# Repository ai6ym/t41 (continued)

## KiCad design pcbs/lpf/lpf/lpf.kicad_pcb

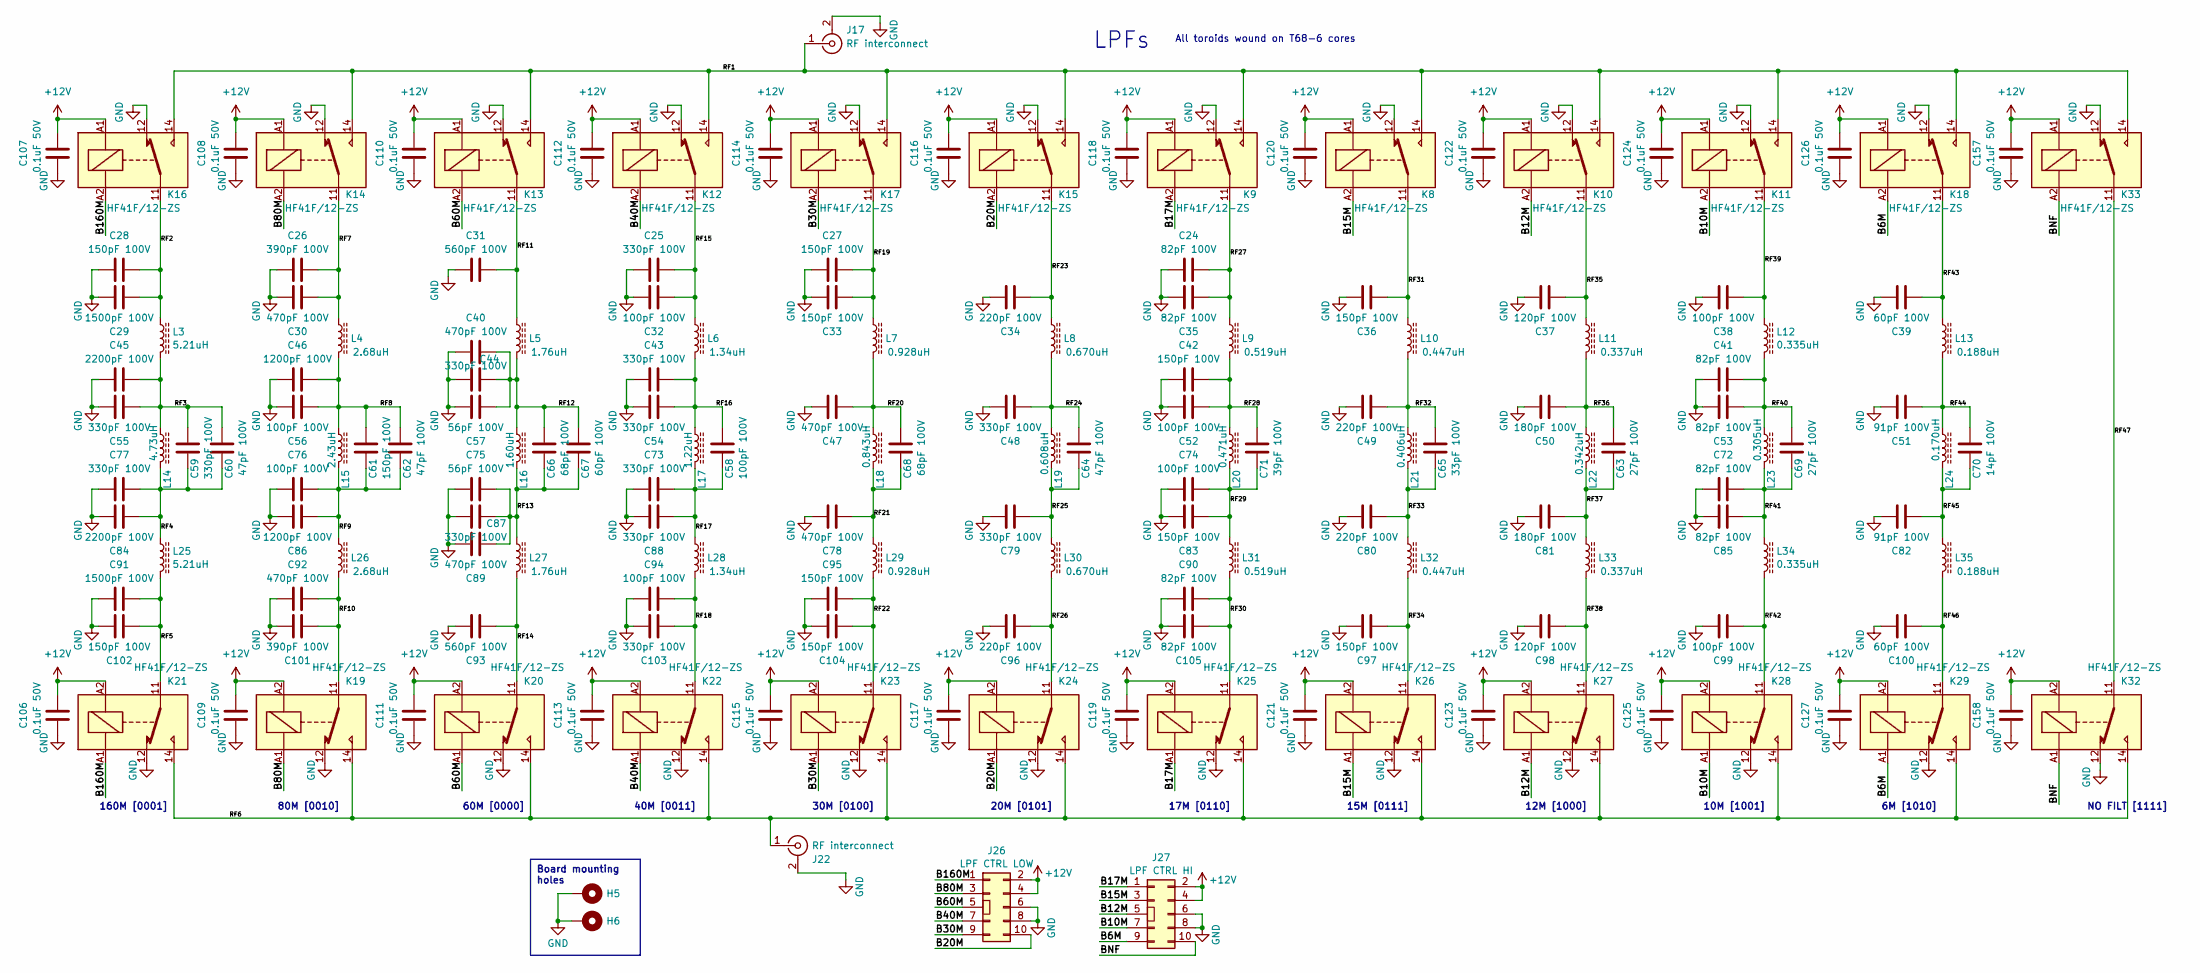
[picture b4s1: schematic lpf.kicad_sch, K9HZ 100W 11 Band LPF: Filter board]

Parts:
C24, C35, C41, C53, C72, C85, C90, C105: 82pF 100V; C_1206_3216Metric; Mouser Part Number 80-C1206C820J1G
C25, C43, C44, C48, C54, C55, C59, C73, C77, C79, C87, C88, C103: 330pF 100V; C_1206_3216Metric; Mouser Part Number 581-12061A331JAT4A
C26, C101: 390pF 100V; C_1206_3216Metric; Mouser Part Number 80-C1206C391J1G
C27, C28, C33, C36, C42, C61, C83, C95, C97, C102, C104: 150pF 100V; C_1206_3216Metric; Mouser Part Number 80-C1206C151J1G
C29, C91: 1500pF 100V; C_1206_3216Metric; Mouser Part Number 80-C1206C152J1GECAUT
C30, C40, C47, C78, C89, C92: 470pF 100V; C_1206_3216Metric; Mouser Part Number 80-C1206C471J1GAC
C31, C93: 560pF 100V; C_1206_3216Metric; Mouser Part Number 581-12061C561JAT2A
C32, C38, C52, C56, C58, C74, C76, C94, C99: 100pF 100V; C_1206_3216Metric; Mouser Part Number 80-C1206C101J1GAULR
C34, C49, C80, C96: 220pF 100V; C_1206_3216Metric; Mouser Part Number 80-C1206C221J1GAC
C37, C98: 120pF 100V; C_1206_3216Metric; Mouser Part Number 77-VJ1206A121JXBMT
C39, C67, C100: 60pF 100V; C_1206_3216Metric; Mouser Part Number 80-C1206C620J1G
C45, C84: 2200pF 100V; C_1206_3216Metric; Mouser Part Number 81-GRM319R72A222JA1D
C46, C86: 1200pF 100V; C_1206_3216Metric; Mouser Part Number 581-12061C122JAT2A
C50, C81: 180pF 100V; C_1206_3216Metric; Mouser Part Number 80-C1206C181J1G
C51, C82: 91pF 100V; C_1206_3216Metric; Mouser Part Number 80-C1206C910J1G
C57, C75: 56pF 100V; C_1206_3216Metric; Mouser Part Number 80-C1206C560J1G
C60, C62, C64: 47pF 100V; C_1206_3216Metric; Mouser Part Number 80-C1206C470J1GAC
C63, C69: 27pF 100V; C_1206_3216Metric; Mouser Part Number 80-C1206C270J1G
C65: 33pF 100V; C_1206_3216Metric; Mouser Part Number 80-C1206C330J1G
C66, C68: 68pF 100V; C_1206_3216Metric; Mouser Part Number 80-C1206C680J1G
C70: 14pF 100V; C_0805_2012Metric; Mouser Part Number 80-C1206C150J1G
C71: 39pF 100V; C_1206_3216Metric; Mouser Part Number 80-C1206C390J1G
C106, C107, C108, C109, C110, C111, C112, C113, C114, C115, C116, C117, C118, C119, C120, C121, C122, C123, C124, C125, C126, C127, C157, C158: 0.1uF 50V; C_1206_3216Metric; Mouser Part Number 581-12065F104K4
H5, H6: MountingHole_4.3mm_M4_DIN965_Pad
J17, J22: RF interconnect; SMA_Amphenol_901-144_Vertical; Mouser Part Number 712-CONSMA001-G
J26: LPF CTRL LOW; IDC-Header_2x05_P2.54mm_Vertical
J27: LPF CTRL HI; IDC-Header_2x05_P2.54mm_Vertical
K8, K9, K10, K11, K12, K13, K14, K15, K16, K17, K18, K19, K20, K21, K22, K23, K24, K25, K26, K27, K28, K29, K32, K33: HF41F/12-ZS; Relay_SPDT_HF41F12-ZS
L3, L25: 5.21uH; T68-6-toroid-vertical
L4, L26: 2.68uH; T68-6-toroid-vertical
L5, L27: 1.76uH; T68-6-toroid-vertical
L6, L28: 1.34uH; T68-6-toroid-vertical
L7, L29: 0.928uH; T68-6-toroid-vertical
L8, L30: 0.670uH; T68-6-toroid-vertical
L9, L31: 0.519uH; T68-6-toroid-vertical
L10, L32: 0.447uH; T68-6-toroid-vertical
L11, L33: 0.337uH; T68-6-toroid-vertical
L12, L34: 0.335uH; T68-6-toroid-vertical
L13, L35: 0.188uH; T68-6-toroid-vertical
L14: 4.73uH; T68-6-toroid-vertical
L15: 2.43uH; T68-6-toroid-vertical
L16: 1.60uH; T68-6-toroid-vertical
L17: 1.22uH; T68-6-toroid-vertical
L18: 0.843uH; T68-6-toroid-vertical
L19: 0.608uH; T68-6-toroid-vertical
L20: 0.471uH; T68-6-toroid-vertical
L21: 0.406uH; T68-6-toroid-vertical
L22: 0.342uH; T68-6-toroid-vertical
L23: 0.305uH; T68-6-toroid-vertical
L24: 0.170uH; T68-6-toroid-vertical

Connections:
+12V: C106.1, C107.1, C108.1, C109.1, C110.1, C111.1, C112.1, C113.1, C114.1, C115.1, C116.1, C117.1, C118.1, C119.1, C120.1, C121.1, C122.1, C123.1, C124.1, C125.1, C126.1, C127.1, C157.1, C158.1, J26.2, J26.4, J27.2, J27.4, K8.A1, K9.A1, K10.A1, K11.A1, K12.A1, K13.A1, K14.A1, K15.A1, K16.A1, K17.A1, K18.A1, K19.A2, K20.A2, K21.A2, K22.A2, K23.A2, K24.A2, K25.A2, K26.A2, K27.A2, K28.A2, K29.A2, K32.A2, K33.A1
/B6M: J27.9, K18.A2, K29.A1
/B10M: J27.7, K11.A2, K28.A1
/B12M: J27.5, K10.A2, K27.A1
/B15M: J27.3, K8.A2, K26.A1
/B17M: J27.1, K9.A2, K25.A1
/B20M: J26.10, K15.A2, K24.A1
/B30M: J26.9, K17.A2, K23.A1
/B40M: J26.7, K12.A2, K22.A1
/B60M: J26.5, K13.A2, K20.A1
/B80M: J26.3, K14.A2, K19.A1
/B160M: J26.1, K16.A2, K21.A1
/BNF: J27.10, K32.A1, K33.A2
/RF1: J17.1 (In), K8.14, K9.14, K10.14, K11.14, K12.14, K13.14, K14.14, K15.14, K16.14, K17.14, K18.14, K33.14
/RF2: C28.2, C29.2, K16.11, L3.1
/RF3: C45.2, C55.2, C59.2, C60.2, L3.2, L14.1
/RF4: C59.1, C60.1, C77.2, C84.2, L14.2, L25.1
/RF5: C91.2, C102.2, K21.11, L25.2
/RF6: J22.1 (In), K19.14, K20.14, K21.14, K22.14, K23.14, K24.14, K25.14, K26.14, K27.14, K28.14, K29.14, K32.14
/RF7: C26.2, C30.2, K14.11, L4.1
/RF8: C46.2, C56.2, C61.2, C62.2, L4.2, L15.1
/RF9: C61.1, C62.1, C76.2, C86.2, L15.2, L26.1
/RF10: C92.2, C101.2, K19.11, L26.2
/RF11: C31.2, K13.11, L5.1
/RF12: C40.2, C44.2, C57.2, C66.2, C67.2, L5.2, L16.1
/RF13: C66.1, C67.1, C75.2, C87.2, C89.2, L16.2, L27.1
/RF14: C93.2, K20.11, L27.2
/RF15: C25.2, C32.2, K12.11, L6.1
/RF16: C43.2, C54.2, C58.2, L6.2, L17.1
/RF17: C58.1, C73.2, C88.2, L17.2, L28.1
/RF18: C94.2, C103.2, K22.11, L28.2
/RF19: C27.2, C33.2, K17.11, L7.1
/RF20: C47.2, C68.2, L7.2, L18.1
/RF21: C68.1, C78.2, L18.2, L29.1
/RF22: C95.2, C104.2, K23.11, L29.2
/RF23: C34.2, K15.11, L8.1
/RF24: C48.2, C64.2, L8.2, L19.1
/RF25: C64.1, C79.2, L19.2, L30.1
/RF26: C96.2, K24.11, L30.2
/RF27: C24.2, C35.2, K9.11, L9.1
/RF28: C42.2, C52.2, C71.2, L9.2, L20.1
/RF29: C71.1, C74.2, C83.2, L20.2, L31.1
/RF30: C90.2, C105.2, K25.11, L31.2
/RF31: C36.2, K8.11, L10.1
/RF32: C49.2, C65.2, L10.2, L21.1
/RF33: C65.1, C80.2, L21.2, L32.1
/RF34: C97.2, K26.11, L32.2
/RF35: C37.2, K10.11, L11.1
/RF36: C50.2, C63.2, L11.2, L22.1
/RF37: C63.1, C81.2, L22.2, L33.1
/RF38: C98.2, K27.11, L33.2
/RF39: C38.2, K11.11, L12.1
/RF40: C41.2, C53.2, C69.2, L12.2, L23.1
/RF41: C69.1, C72.2, C85.2, L23.2, L34.1
/RF42: C99.2, K28.11, L34.2
/RF43: C39.2, K18.11, L13.1
/RF44: C51.2, C70.2, L13.2, L24.1
/RF45: C70.1, C82.2, L24.2, L35.1
/RF46: C100.2, K29.11, L35.2
/RF47: K32.11, K33.11
GND: C24.1, C25.1, C26.1, C27.1, C28.1, C29.1, C30.1, C31.1, C32.1, C33.1, C34.1, C35.1, C36.1, C37.1, C38.1, C39.1, C40.1, C41.1, C42.1, C43.1, C44.1, C45.1, C46.1, C47.1, C48.1, C49.1, C50.1, C51.1, C52.1, C53.1, C54.1, C55.1, C56.1, C57.1, C72.1, C73.1, C74.1, C75.1, C76.1, C77.1, C78.1, C79.1, C80.1, C81.1, C82.1, C83.1, C84.1, C85.1, C86.1, C87.1, C88.1, C89.1, C90.1, C91.1, C92.1, C93.1, C94.1, C95.1, C96.1, C97.1, C98.1, C99.1, C100.1, C101.1, C102.1, C103.1, C104.1, C105.1, C106.2, C107.2, C108.2, C109.2, C110.2, C111.2, C112.2, C113.2, C114.2, C115.2, C116.2, C117.2, C118.2, C119.2, C120.2, C121.2, C122.2, C123.2, C124.2, C125.2, C126.2, C127.2, C157.2, C158.2, H5.1, H6.1, J17.2 (Ext), J22.2 (Ext), J26.6, J26.8, J27.6, J27.8, K8.12, K9.12, K10.12, K11.12, K12.12, K13.12, K14.12, K15.12, K16.12, K17.12, K18.12, K19.12, K20.12, K21.12, K22.12, K23.12, K24.12, K25.12, K26.12, K27.12, K28.12, K29.12, K32.12, K33.12

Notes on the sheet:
Board mounting holes
6M [1010]
160M [0001]
15M [0111]
All toroids wound on T68-6 cores
10M [1001]
30M [0100]
20M [0101]
40M [0011]
60M [0000]
LPFs
17M [0110]
12M [1000]
80M [0010]
NO FILT [1111]

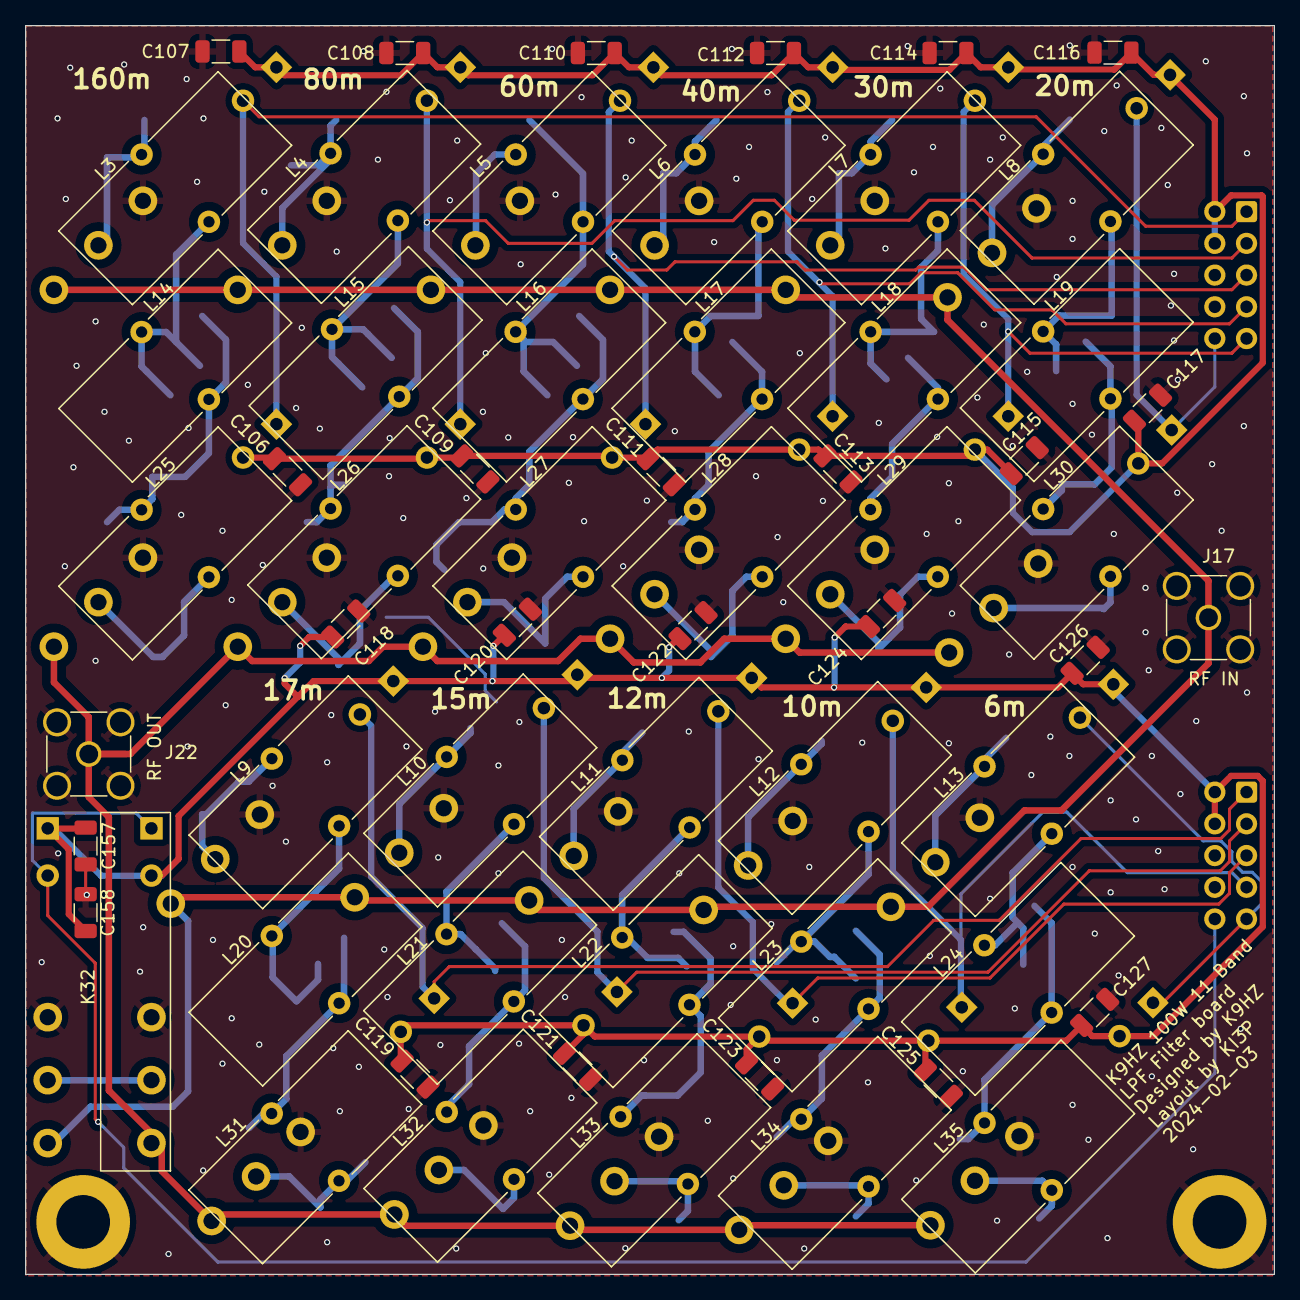
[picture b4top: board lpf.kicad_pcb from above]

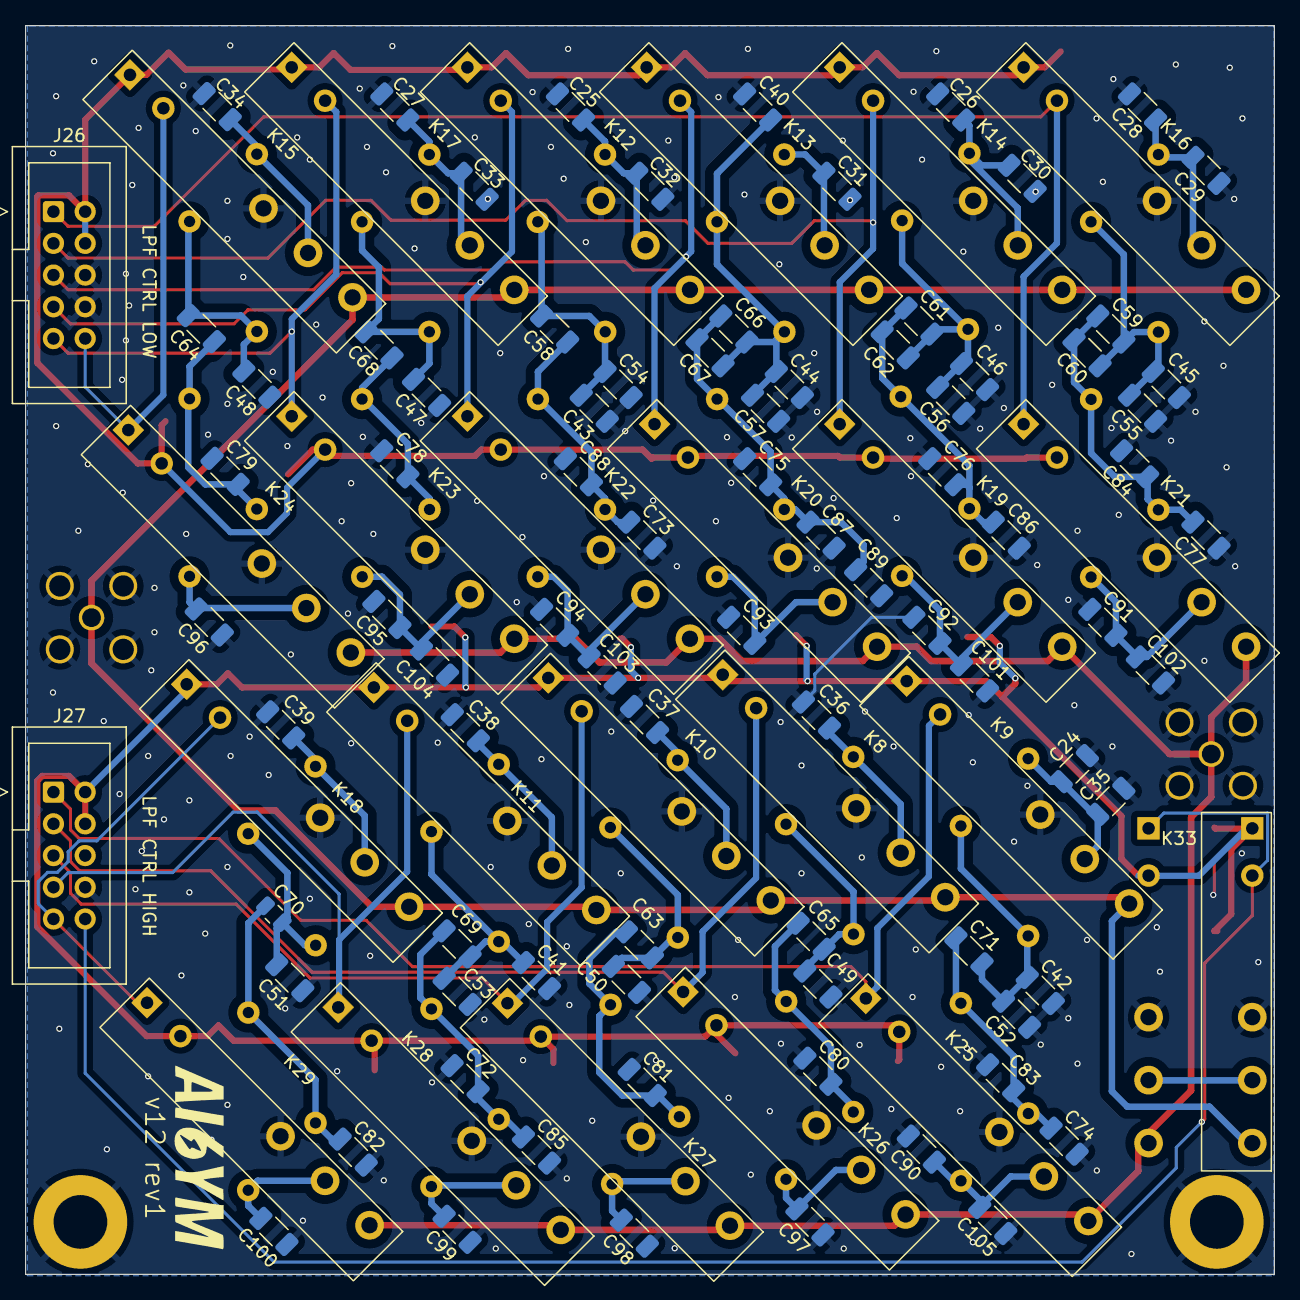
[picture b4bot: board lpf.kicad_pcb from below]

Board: 4 copper layers, 100.0 x 100.0 mm, 169 parts (107 on the bottom side), 61 nets.

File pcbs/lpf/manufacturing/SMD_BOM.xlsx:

|  |  | xxxx xxxx xxxxx xxPCS BOM (Sample Bill of Materials)
Item # | *Designator | *Qty | Manufacturer | *Mfg Part # | Description / Value | *Package/Footprint | Type | Your Instructions / Notes
1 | C70 | 1 | Murata Electronics | GQM2195C2E140JB12D | 14pF 200V | 0805 | SMD
2 | C63, C69 | 2 | YAGEO | CC1206JKNPOCBN270 | 27pF 200V | 1206 | SMD
3 | C65 | 1 | YAGEO | CC1206JKNPOCBN330 | 33pF 200V | 1206 | SMD
4 | C71 | 1 | KEMET | C1206C390J2GACTU | 39 pF 200V | 1206 | SMD
5 | C60, C62, C64 | 3 | YAGEO | CC1206JRNPOABN470 | 47pF 200V | 1206 | SMD
6 | C57, C75 | 2 | KEMET | C1206C560J2GACTU | 56pF 200V | 1206 | SMD
7 | C39, C67, C100 | 3 | Kyocera AVX | 12062A600FAT2A | 60pF 200V | 1206 | SMD
8 | C66, C68 | 2 | KEMET | C1206C680J2GACTU | 68pF 200V | 1206 | SMD
9 | C24, C35, C41, C53, C72, C85, C90, C105 | 8 | KEMET | C1206C820J2GACTU | 82pF 200V | 1206 | SMD
10 | C51, C82 | 2 | Cal-Chip Electronics Inc. | CHV1206N500910JCT | 91pF 200V | 1206 | SMD
11 | C32, C38, C52, C56, C58, C74, C76, C94, C99 | 9 | Kyocera AVX | 12062A101JAT2A | 100pF 200V | 1206 | SMD
12 | C37, C98 | 2 | Kyocera AVX | 12062A121JAT2A | 120pF 200V | 1206 | SMD
13 | C27, C28, C33, C36, C42, C61, C83, C95, C97, C102, C104 | 11 | YAGEO | CC1206JRNPOABN151 | 150pF 200V | 1206 | SMD
14 | C50, C81 | 2 | Kyocera AVX | 12062A181JAT2A | 180pF 200V | 1206 | SMD
15 | C34, C49, C80, C96 | 4 | Kyocera AVX | 12062A221JAT2A | 220pF 200V | 1206 | SMD
16 | C25, C43, C44, C48, C54, C55, C59, C73, C77, C79, C87, C88, C103 | 13 | Kyocera AVX | 12062A331JAT2A | 330pF 200V | 1206 | SMD
17 | C26, C101 | 2 | Kyocera AVX | 12062A391JAT2A | 390pF 200V | 1206 | SMD
18 | C30, C40, C47, C78, C89, C92 | 6 | Yageo | CC1206JRNPOABN471 | 470pF 200V | 1206 | SMD
19 | C31, C93 | 2 | KEMET | C1206C561J2GACTU | 560pF 200V | 1206 | SMD
20 | C46, C86 | 2 | Kyocera AVX | 12062A122JAT2A | 1200pF 200V | 1206 | SMD
21 | C29, C91 | 2 | YAGEO | CC1206JRNPOABN152 | 1500pF 200V | 1206 | SMD
22 | C45, C84 | 2 | Kyocera AVX | 12062C222JAT2A | 2200pF 200V | 1206 | SMD
23 | C106, C107, C108, C109, C110, C111, C112, C113, C114, C115, C116, C117, C118, C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 | 24 | KEMET | C1206C104K5RACTU | 0.1uF 50V | 1206 | SMD
Need a quick and accurante quote? Need an efficient production? Please read SMT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
Click for Instructions on How to Create a BOM

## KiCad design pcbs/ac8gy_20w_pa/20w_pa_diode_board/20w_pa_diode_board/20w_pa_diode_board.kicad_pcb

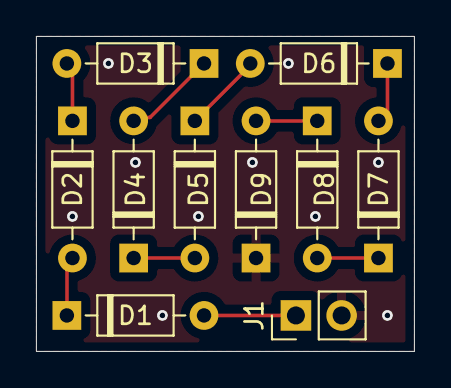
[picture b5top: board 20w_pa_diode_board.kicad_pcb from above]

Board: 2 copper layers, 21.0 x 17.5 mm, 10 parts (0 on the bottom side), 10 nets.

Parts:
D1, D2, D3, D4, D5, D6, D7, D8, D9: 1N4148; D_DO-35_SOD27_P7.62mm_Horizontal
J1: Conn_01x02_Pin; PinHeader_1x02_P2.54mm_Vertical

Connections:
GND: D9.1 (K), J1.2
unnamed: D1.2 (A), J1.1
unnamed: D1.1 (K), D2.2 (A)
unnamed: D2.1 (K), D3.2 (A)
unnamed: D3.1 (K), D4.2 (A)
unnamed: D4.1 (K), D5.2 (A)
unnamed: D5.1 (K), D6.2 (A)
unnamed: D6.1 (K), D7.2 (A)
unnamed: D7.1 (K), D8.2 (A)
unnamed: D8.1 (K), D9.2 (A)

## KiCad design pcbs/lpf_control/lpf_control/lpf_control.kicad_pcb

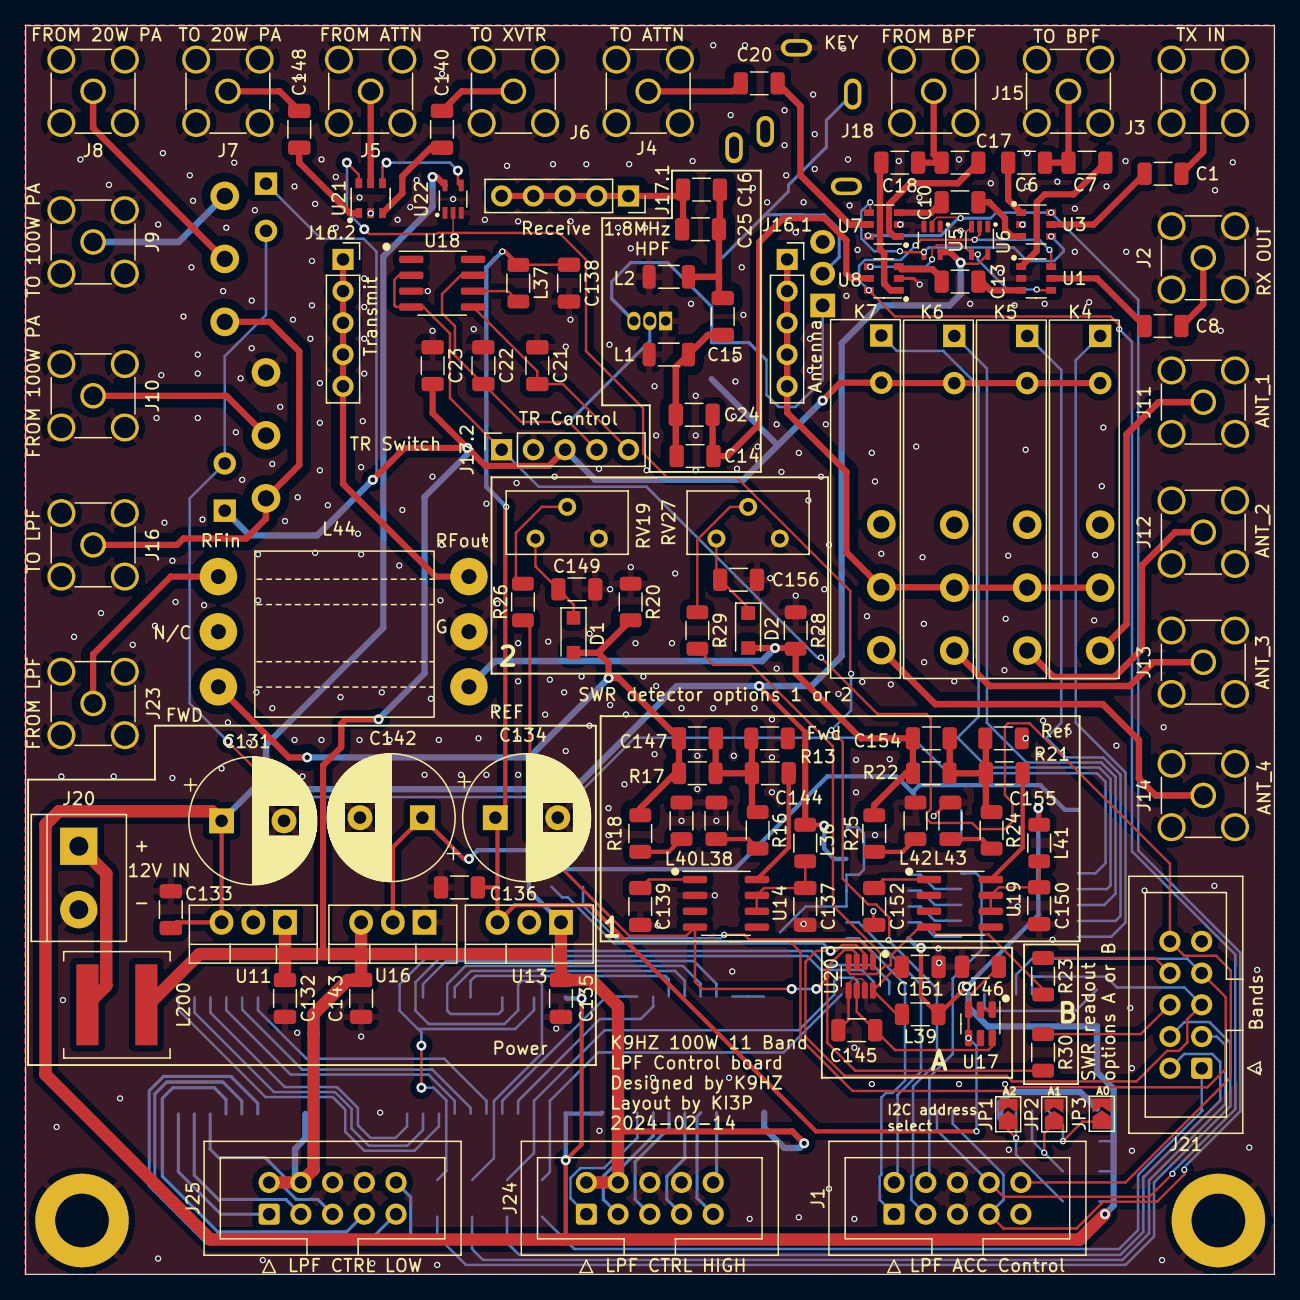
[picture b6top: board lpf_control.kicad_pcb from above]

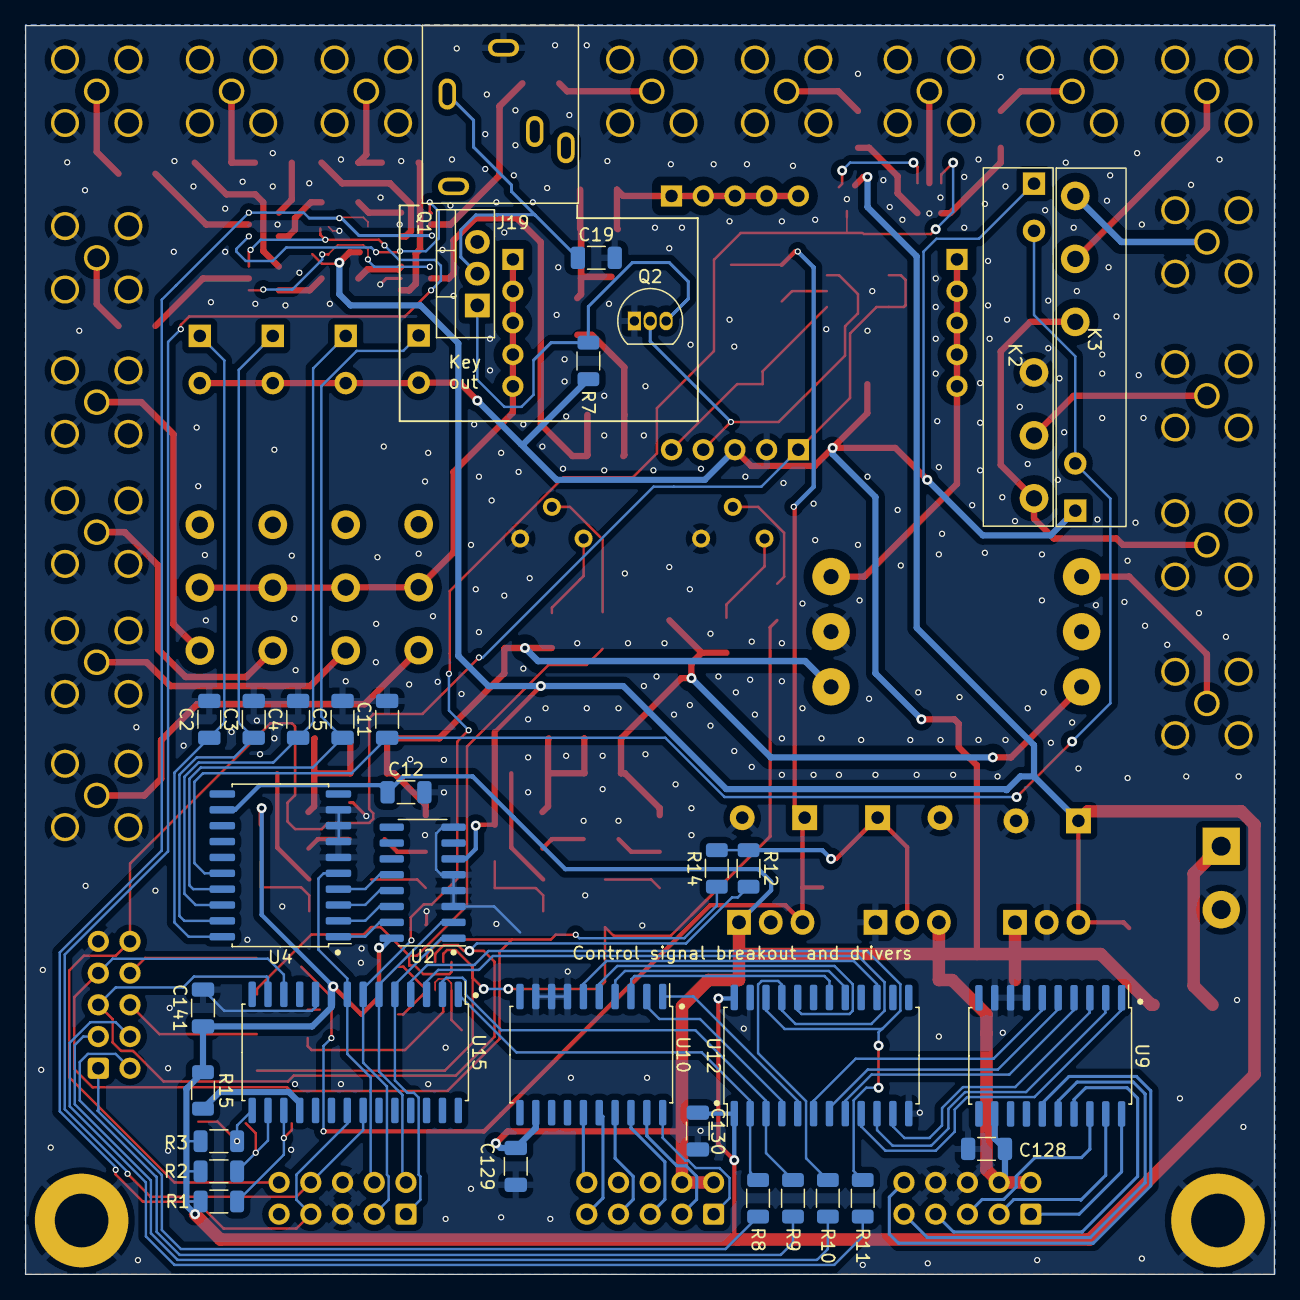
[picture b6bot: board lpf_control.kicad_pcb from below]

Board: 4 copper layers, 100.0 x 100.0 mm, 155 parts (33 on the bottom side), 128 nets.

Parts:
C1, C2, C3, C4, C5, C6, C7, C8, C10, C11, C12, C13, C17, C18, C20, C21, C22, C23, C128, C129, C130, C137, C138, C139, C140, C141, C148, C150, C151, C152: 0.1uF 50V; C_1206_3216Metric
C14, C16: 1800pF 50V; C_1206_3216Metric
C15: 1000pF 50V; C_1206_3216Metric
C19: 15nF 50V; C_1206_3216Metric
C24, C25: 100pF 50V; C_1206_3216Metric
C131, C134: 220uF 16V; CP_Radial_D10.0mm_P5.00mm
C132, C133, C135, C136, C146: 1uF 50V; C_1206_3216Metric
C142: 100uF 6V; CP_Radial_D10.0mm_P5.00mm
C143, C145: 10uF 50V; C_1206_3216Metric
C144, C149, C155, C156: 10nF 50V; C_1206_3216Metric
C147, C154: 10pF 50V; C_1206_3216Metric
D1, D2: BAS70H,115; D_SOD-123F
H1, H2: MountingHole_4.3mm_M4_DIN965_Pad
J1: LPF ACC Control; IDC-Header_2x05_P2.54mm_Vertical
J2: TO_RECEIVER; SMA_Amphenol_901-144_Vertical
J3: FROM TX; SMA_Amphenol_901-144_Vertical
J4: TO ATTN; SMA_Amphenol_901-144_Vertical
J5: FROM ATTN; SMA_Amphenol_901-144_Vertical
J6: TO XVTR; SMA_Amphenol_901-144_Vertical
J7: TO 20W PA; SMA_Amphenol_901-144_Vertical
J8: FROM 20W PA; SMA_Amphenol_901-144_Vertical
J9: TO 100W PA; SMA_Amphenol_901-144_Vertical
J10: FROM 100W PA; SMA_Amphenol_901-144_Vertical
J11: ANT-1; SMA_Amphenol_901-144_Vertical
J12: ANT-2; SMA_Amphenol_901-144_Vertical
J13: ANT-3; SMA_Amphenol_901-144_Vertical
J14: ANT-4; SMA_Amphenol_901-144_Vertical
J15: TO BPF; SMA_Amphenol_901-144_Vertical
J16: TO LPF; SMA_Amphenol_901-144_Vertical
J16.1: ANTENNA; PinSocket_1x05_P2.54mm_Vertical
J16.2: TRANSMIT; PinSocket_1x05_P2.54mm_Vertical
J17.1: RECEIVE; PinSocket_1x05_P2.54mm_Vertical
J17.2: TR CTL; PinSocket_1x05_P2.54mm_Vertical
J18: FROM BPF; SMA_Amphenol_901-144_Vertical
J19: KEY OUT; Jack_3.5mm_STX-3081_Horizontal
J20: 12-13.8V; TerminalBlock_bornier-2_P5.08mm
J21: Bands; IDC-Header_2x05_P2.54mm_Vertical
J23: FROM LPF; SMA_Amphenol_901-144_Vertical
J24: LPF CTRL HI; IDC-Header_2x05_P2.54mm_Vertical
J25: LPF CTRL LOW; IDC-Header_2x05_P2.54mm_Vertical
JP1, JP2, JP3: SolderJumper_2_Open; SolderJumper-2_P1.3mm_Open_TrianglePad1.0x1.5mm
K2, K3, K4, K5, K6, K7: HF41F/12-ZS; Relay_SPDT_HF41F12-ZS
L1, L2: 3.3uH; L_1206_3216Metric
L36, L37, L39, L41: FB; R_1206_3216Metric
L38, L40, L42, L43: 22nH; R_1206_3216Metric
L44: 6_pin_transformer; Toroid_6Pin_BinocularCore_13.3mm_14.35mm
L200: 10uH 20%; L_Coilcraft_XAL7020-102
Q1: IRF630; TO-220-3_Vertical
Q2: 2N7000; TO-92_Inline
R1, R2, R3, R12, R14, R15: 2k2; R_1206_3216Metric
R7, R26, R29: 10k; R_1206_3216Metric
R8, R9, R10, R11, R23, R30: 0; R_1206_3216Metric
R13, R20, R21, R28: 52R3; R_1206_3216Metric
R16, R17, R18, R22, R24, R25: R_1206_3216Metric
RV19, RV27: 22k; Potentiometer_Bourns_3296Y_Vertical
U1, U3, U7, U8, U21: MASWSS0179; MASWSS0179-SOT-26
U2: 74HC237; SOIC-16_3.9x9.9mm_P1.27mm
U4, U9, U10: ULN2803C; SOIC-20W_7.5x12.8mm_P1.27mm
U5, U6, U22: SN74LVC1G04DCK; SOT-SC70
U11: LM7805CT; TO-220-3_Vertical
U12: CD74HC4514M96; SOIC-24W_7.5x15.4mm_P1.27mm
U13: L7808; TO-220-3_Vertical
U14, U19: AD8307; SOIC-8_3.9x4.9mm_P1.27mm
U15: MCP23017_SO; SOIC-28W_7.5x17.9mm_P1.27mm
U16: LM1117T-3.3; TO-220-3_Vertical
U17: REF3440IDBVR; SOT-23-6
U18: TC4428; SOIC-8_3.9x4.9mm_P1.27mm
U20: AD7991YRJZ; SOT-23-8

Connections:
+3V3: C142.1, R12.2, R14.2, U16.2 (VO)
+5V: C130.1, C131.1, C133.1, C141.1, L36.2, L39.2, L41.2, R1.2, R2.2, R3.2, R15.1, U2.6 (E2), U2.16 (VCC), U5.5 (VCC), U6.5 (VCC), U11.3 (VO), U12.1 (~LE), U12.24 (VCC), U15.9 (VDD), U22.5 (VCC)
+8V: C134.1, C136.1, C138.1, C146.2, L37.1, U13.3 (OUT), U17.3 (ENABLE), U17.4 (VIN)
+12V: C12.1, C23.2, C128.1, C129.1, C132.1, C135.1, C143.1, J17.2.3, J24.2, J24.4, J25.2, J25.4, K2.A1, K3.A1, K4.A2, K5.A2, K6.A2, K7.A2, L200.2, R7.1, U4.12 (COM), U9.12 (COM), U10.12 (COM), U11.1 (VI), U13.1 (IN), U16.3 (VI)
/6M: J24.9, U10.16 (O5)
/8R ~TX: C22.2, J17.2.4, Q2.2 (G), U18.7 (~OUT_A)
/8T TX: C21.2, J17.2.5, U18.5 (OUT_B)
/10M: J24.7, U10.17 (O4)
/12M: J24.5, U10.18 (O3)
/15M: J24.3, U10.19 (O2)
/17M: J24.1, U10.20 (O1)
/20M: J25.10, U9.15 (O6)
/30M: J25.9, U9.16 (O5)
/40M: J25.7, U9.17 (O4)
/60M: J25.5, U9.18 (O3)
/80M: J25.3, U9.19 (O2)
/100W_PA_SEL: C11.1, K2.A2, K3.A2, U4.16 (O5)
/160M: J25.1, U9.20 (O1)
/ANT1_SEL: C2.1, K4.A1, U4.20 (O1)
/ANT2_SEL: C3.1, K5.A1, U4.19 (O2)
/ANT3_SEL: C4.1, K6.A1, U4.18 (O3)
/ANT4_SEL: C5.1, K7.A1, U4.17 (O4)
/BIT0: J21.1, R8.2
/BIT1: J21.2, R9.2
/BIT2: J21.3, R10.2
/BIT3: J21.4, R11.2
/FWD: R26.1, R30.2, U14.4 (OUT), U20.3 (Vin0)
/FWD_V: J21.6, R30.1
/LPF_TO_SWR: J23.1 (In), L44.1
/NF: J24.10, U10.15 (O6)
/REF: R23.2, R29.2, U19.4 (OUT), U20.4 (Vin1)
/REF_V: J21.8, R23.1
/RF1: C1.2, J3.1 (In)
/RF7: C20.1, J4.1 (In)
/RF17: C140.2, J6.1 (In)
/RF18: C148.1, J7.1 (In)
/RF19: J8.1 (In), K2.11
/RF20: J9.1 (In), K2.14
/RF21: J16.1 (In), K2.12, K3.14
/RF22: J10.1 (In), K3.11
/RF23: J16.1.1, J16.1.2, J16.1.3, J16.1.4, J16.1.5, K4.11, K5.11, K6.11, K7.11
/RF24: J11.1 (In), K4.14
/RF27: J14.1 (In), K7.14
/RF28: C16.2, C25.2, J17.1.1, J17.1.2, J17.1.3, J17.1.4, J17.1.5
/RF29: C15.2, C16.1, C25.1, L2.1
/RF30: C14.2, C15.1, C24.2, L1.1
/RF34: C8.2, J2.1 (In)
/RF35: C147.2, D1.2 (A), L44.3, R17.1, R18.2, R20.2
/RF36: C154.2, D2.2 (A), L44.4, R22.1, R25.2, R28.2
/RF37: C154.1, C155.2, R21.2, R22.2, R24.2
/RF38: C144.2, C147.1, R13.2, R16.2, R17.2
/RRF2: C1.1, U3.5 (RFC)
/RRF3: C6.1, U3.1 (RF1)
/RRF4: C10.2, U3.3 (RF2)
/RRF5: C10.1, U7.3 (RF2)
/RRF6: C20.2, U7.5 (RFC)
/RRF8: C6.2, C7.1, J15.1 (In)
/RRF9: C17.2, C18.1, J18.1 (In)
/RRF10: C17.1, U7.1 (RF1)
/RRF11: C7.2, U1.1 (RF1)
/RRF12: C13.2, U8.3 (RF2)
/RRF13: C18.2, U8.1 (RF1)
/RRF14: J5.1 (In), U21.5 (RFC)
/RRF15: C140.1, U21.3 (RF2)
/RRF16: C148.2, U21.1 (RF1)
/RRF25: J12.1 (In), K5.14
/RRF26: J13.1 (In), K6.14
/RRF31: C14.1, C24.1, U8.5 (RFC)
/RRF32: C13.1, U1.3 (RF2)
/RRF33: C8.1, U1.5 (RFC)
/RX_BPF_SEL: J1.8, U1.6 (V1), U6.2, U8.6 (V1), U15.22 (GPA1)
/SCL: J21.7, R14.1, U15.12 (SCK), U20.1 (SCL)
/SDA: J21.5, R12.1, U15.13 (SDA), U20.2 (SDA)
/SWR_TO_PIN_DIODE_TR: J16.2.1, J16.2.2, J16.2.3, J16.2.4, J16.2.5, L44.2
/TX: J1.10, J17.2.1, J21.10, U18.2 (IN_A), U18.4 (IN_B)
/TX_BPF_SEL: J1.7, U3.6 (V1), U5.2, U7.6 (V1), U15.21 (GPA0)
/XVTR_SEL: J1.3, U15.7 (GPB6), U21.6 (V1), U22.2
GND: C2.2, C3.2, C4.2, C5.2, C11.2, C12.2, C19.2, C21.1, C22.1, C23.1, C128.2, C129.2, C130.2, C131.2, C132.2, C133.2, C134.2, C135.2, C136.2, C137.2, C138.2, C139.2, C141.2, C142.2, C143.2, C145.2, C146.1, C149.2, C150.2, C151.2, C152.2, C156.2, H1.1, H2.1, J1.5, J1.6, J2.2 (Ext), J3.2 (Ext), J4.2 (Ext), J5.2 (Ext), J6.2 (Ext), J7.2 (Ext), J8.2 (Ext), J9.2 (Ext), J10.2 (Ext), J11.2 (Ext), J12.2 (Ext), J13.2 (Ext), J14.2 (Ext), J15.2 (Ext), J16.2 (Ext), J17.2.2, J18.2 (Ext), J19.S, J20.2, J21.9, J23.2 (Ext), J24.6, J24.8, J25.6, J25.8, JP1.2 (B), JP2.2 (B), JP3.2 (B), K3.12, L1.2, L2.2, L38.2, L40.2, L42.2, L43.2, L44.5, Q1.3 (S), Q2.1 (S), R13.1, R20.1, R21.1, R28.1, RV19.3, RV27.3, U1.2 (GND), U2.3 (A2), U2.4 (~LE), U2.5 (~E1), U2.8 (GND), U3.2 (GND), U4.6 (I6), U4.7 (I7), U4.8 (I8), U4.9 (GND), U5.3 (GND), U6.3 (GND), U7.2 (GND), U8.2 (GND), U9.7 (I7), U9.8 (I8), U9.9 (GND), U10.7 (I7), U10.8 (I8), U10.9 (GND), U11.2 (GND), U12.12 (GND), U12.23 (~E), U13.2 (GND), U14.2 (COM), U15.10 (VSS), U16.1 (GND), U17.1 (GNDF), U17.2 (GNDS), U18.3 (GND), U19.2 (COM), U20.5 (Vin2), U20.7 (GND), U21.2 (GND), U22.3 (GND)
unnamed: C149.1, D1.1 (K), RV19.1
unnamed: C156.1, D2.1 (K), RV27.1
unnamed: J1.1, U2.1 (A0), U15.5 (GPB4)
unnamed: J1.2, U2.2 (A1), U15.6 (GPB5)
unnamed: J1.4, U4.5 (I5), U15.8 (GPB7)
unnamed: J20.1, L200.1
unnamed: JP1.1 (A), R1.1, U15.17 (A2)
unnamed: JP2.1 (A), R2.1, U15.16 (A1)
unnamed: JP3.1 (A), R3.1, U15.15 (A0)
unnamed: L38.1, R16.1
unnamed: L40.1, R18.1
unnamed: L42.1, R25.1
unnamed: L43.1, R24.1
unnamed: C19.1, J19.T, Q1.2 (D)
unnamed: Q1.1 (G), Q2.3 (D), R7.2
unnamed: R26.2, RV19.2
unnamed: R29.1, RV27.2
unnamed: U1.4 (V2), U6.4, U8.4 (V2)
unnamed: U2.15 (Y0), U4.1 (I1)
unnamed: U2.14 (Y1), U4.2 (I2)
unnamed: U2.13 (Y2), U4.3 (I3)
unnamed: U2.12 (Y3), U4.4 (I4)
unnamed: U3.4 (V2), U5.4, U7.4 (V2)
unnamed: U10.1 (I1), U12.5 (Y6)
unnamed: U10.2 (I2), U12.4 (Y7)
unnamed: U10.3 (I3), U12.18 (Y8)
unnamed: U10.4 (I4), U12.17 (Y9)
unnamed: U10.5 (I5), U12.20 (Y10)
unnamed: U10.6 (I6), U12.15 (Y15)
unnamed: R8.1, U12.2 (A0), U15.1 (GPB0)
unnamed: R9.1, U12.3 (A1), U15.2 (GPB1)
unnamed: R10.1, U12.21 (A2), U15.3 (GPB2)
unnamed: R11.1, U12.22 (A3), U15.4 (GPB3)
unnamed: U9.3 (I3), U12.11 (Y0)
unnamed: U9.1 (I1), U12.9 (Y1)
unnamed: U9.2 (I2), U12.10 (Y2)
unnamed: U9.4 (I4), U12.8 (Y3)
unnamed: U9.5 (I5), U12.7 (Y4)
unnamed: U9.6 (I6), U12.6 (Y5)
unnamed: C137.1, L36.1, U14.6 (ENB), U14.7 (VPS)
unnamed: C139.1, U14.1 (INM)
unnamed: C144.1, U14.8 (INP)
unnamed: R15.2, U15.18 (~RESET)
unnamed: C145.1, U17.6 (OUT_F), U20.6 (Vin3/Vref)
unnamed: L37.2, U18.6 (VDD)
unnamed: C150.1, L41.1, U19.6 (ENB), U19.7 (VPS)
unnamed: C152.1, U19.1 (INM)
unnamed: C155.1, U19.8 (INP)
unnamed: C151.1, L39.1, U20.8 (Vdd)
unnamed: U21.4 (V2), U22.4

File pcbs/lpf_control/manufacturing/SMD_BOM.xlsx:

|  |  | xxxx xxxx xxxxx xxPCS BOM (Sample Bill of Materials)
Item # | *Designator | *Qty | Manufacturer | *Mfg Part # | Description / Value | *Package/Footprint | Type | Your Instructions / Notes
1 | C15 | 1 | KEMET | C1206C102K5RAC | 1000pF 50V | 1206 | SMD
2 | C24, C25 | 2 | KEMET | C1206C301F1HACAUTO | 300 pF 50V | 1206 | SMD
3 | C14, C16 | 2 | KEMET | C1206C162K3HACTU | 1600 pF 50V | 1206 | SMD
4 | L1, L2 | 2 | Vishay / Dale | ILSB1206ER3R3K | 3.3uH | 1206 | SMD
5 | C1, C2, C3, C4, C5, C6, C7, C8, C9, C10, C11, C12, C13, C17, C18, C20, C21, C22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 | 31 | KEMET | C1206C104K5RACTU | 0.1uF 50V | 1206 | SMD
6 | C19 | 1 | Kyocera AVX | 12065C153KAT2A | 15nF 50V | 1206 | SMD
7 | C132, C133, C135, C136, C146 | 5 | Samsung Electro-Mechanics | CL31B105KBHNNNE | 1uF 50V SMD 1206 Capacitor | 1206 | SMD
8 | C143, C145 | 2 | KEMET | C1206C106K4PACTU | 10uF 16V SMD 1206 Capacitor | 1206 | SMD
9 | L36, L37, L39, L41 | 4 | Laird Perfomance Materials | HZ1206E601R-10 | FB SMD 1206 600 Ohm 1A | 1206 | SMD
10 | L200 | 1 | Murata Electronics | 1264EY-100M=P3 | 10uH 20% Power Inductor | 2424 | SMD
11 | R7 | 1 | Vishay / Dale | CRCW120610K0FKEA | 10K Ohm SMD 1206 Resistor | 1206 | SMD
12 | R1, R2, R3, R12, R14, R15 | 6 | Bourns | CR1206-JW-222ELF | 2.2K Ohm SMD 1206 Resistor | 1206 | SMD
13 | U1, U3, U7, U8, U21 | 5 | MACOM | MASWSS0179TR-3000 | MASWSS0179 | SOT-26 | SMD
14 | U2 | 1 | Toshiba | 74HC237D(BJ) | 74HC237 | SOIC-16 | SMD
15 | U4, U9, U10 | 3 | Texas Instruments | ULN2803CDWR | ULN2803A | SOIC-20 | SMD
16 | U5, U6, U22 | 3 | Texas Instruments | SN74LVC1G04DCKR | 74LVC1G04DCKR | SC70-5 | SMD
17 | U12 | 1 | Texas Instruments | CD74HC4514M96 | CD74HC4514M96 | SOIC-24 | SMD
18 | U15 | 1 | Microchip Technology | MCP23017-E/SO | MCP23017_SO | SOIC-28 | SMD
19 | U18 | 1 | Microchip Technology | TC4428ACOA | TC4428 | SOIC-8 | SMD
20 | C144, C155 | 2 | KEMET | C1206C103K5RAC7210 | 10nF 50V | 1206 | SMD
21 | C147, C154 | 2 | KEMET | C1206C100J5GAC | 10pF 50V | 1206 | SMD
22 | L38, L40, L42, L43 | 4 | Abracon | AISC-1206-22NJ-T | 22nH SMD 1206 Inductor | 1206 | SMD
23 | R13, R21 | 2 | Yageo | RC1206FR-0752R3L | 52.3 Ohm SMD 1206 Resistor | 1206 | SMD
24 | R16, R18, R24, R25 | 4 | Vishay / Dale | CRCW120654R9FKEA | 54.9 Ohm SMD 1206 Resistor | 1206 | SMD
25 | R17, R22 | 2 | Vishay / Dale | CRCW1206499RFKEB | 499 Ohm SMD 1206 Resistor | 1206 | SMD
26 | U14, U19 | 2 | Analog Devices | AD8307ARZ-RL7 | AD8307 | SOIC-8 | SMD
27 | U17 | 1 | Texas Instruments | REF3440IDBVR | REF3440IDBVR | SOT-23-6 | SMD
28 | U20 | 1 | Analog Devices | AD7991YRJZ-0500RL7 | AD7991YRJZ | SOT-23-8 | SMD
Need a quick and accurante quote? Need an efficient production? Please read SMT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
Click for Instructions on How to Create a BOM

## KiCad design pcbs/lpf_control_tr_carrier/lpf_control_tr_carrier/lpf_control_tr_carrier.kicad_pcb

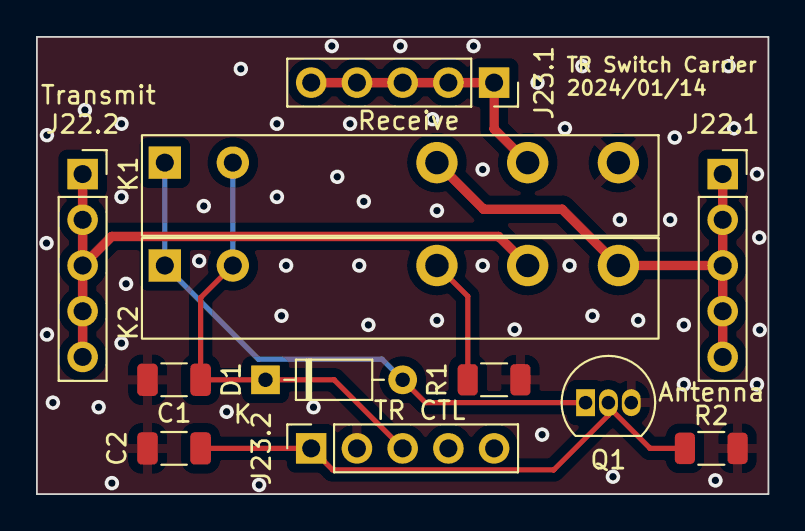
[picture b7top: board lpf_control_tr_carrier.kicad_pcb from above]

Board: 2 copper layers, 40.6 x 25.4 mm, 12 parts (0 on the bottom side), 8 nets.

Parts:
C1, C2: 0.1uF 50V; C_1206_3216Metric
D1: 1N4148; D_DO-35_SOD27_P7.62mm_Horizontal
J22.1: ANTENNA; PinSocket_1x05_P2.54mm_Vertical
J22.2: TRANSMIT; PinSocket_1x05_P2.54mm_Vertical
J23.1: RECEIVE; PinSocket_1x05_P2.54mm_Vertical
J23.2: TR CTL; PinSocket_1x05_P2.54mm_Vertical
K1, K2: HF41F/12-ZS; Relay_SPDT_HF41F12-ZS
Q1: BS170; TO-92_Inline
R1: 50R; R_1206_3216Metric
R2: 10k; R_1206_3216Metric

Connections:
/ANT: J22.1.1, J22.1.2, J22.1.3, J22.1.4, J22.1.5, K1.12, K2.14
/TX: C2.1, J23.2.1, Q1.2 (G), R2.1
GND: C1.2, C2.2, J23.2.2, K1.14, Q1.3 (S), R1.2, R2.2
unnamed: D1.2 (A), K1.A1, K2.A1, Q1.1 (D)
unnamed: C1.1, D1.1 (K), J23.2.3, K1.A2, K2.A2
unnamed: J22.2.1, J22.2.2, J22.2.3, J22.2.4, J22.2.5, K2.11
unnamed: J23.1.1, J23.1.2, J23.1.3, J23.1.4, J23.1.5, K1.11
unnamed: K2.12, R1.1

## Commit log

2024-08-17 Initial commit of hardware files as used in manufacturing.
2024-09-03 Replacing K9HZ amplifier with updated AC8GY design, at the request of K9HZ.
2024-09-03 Added front panel test software and soft on / off ATTiny sketch.
2024-09-18 Initial commits of BPF test, i2c scan, and main software.
2024-09-30 Restored k9hz amp, without closed source materials.
2024-10-27 Adding draft of front panel.
2024-11-17 Updating main Teensy software for T41 SDT. Based on https://github.com/KI3P/SDTVer050.0/commit/2f7bccf308826ce5f91d40895a645f1f4040332b
2024-11-17 Removing previous main software release. Keeping software in version-less directory.
2024-11-24 Initial commit of enclosure for T41 w/7" display.
2024-11-30 Adding powerpole mount.
2025-01-03 Adding print sheets for T41 enclosure.
2025-04-08 Modified SDT_main to only display ownership on splash screen when a callsign is set.
2025-04-08 Updating SDT_Main README with environment setup instructions.
